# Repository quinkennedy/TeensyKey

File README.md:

One teensy, one key

A small project to attach one keyboard switch to a teensy.
This will be primarily done as a single-sided board for milling
on a hobbyist CNC.

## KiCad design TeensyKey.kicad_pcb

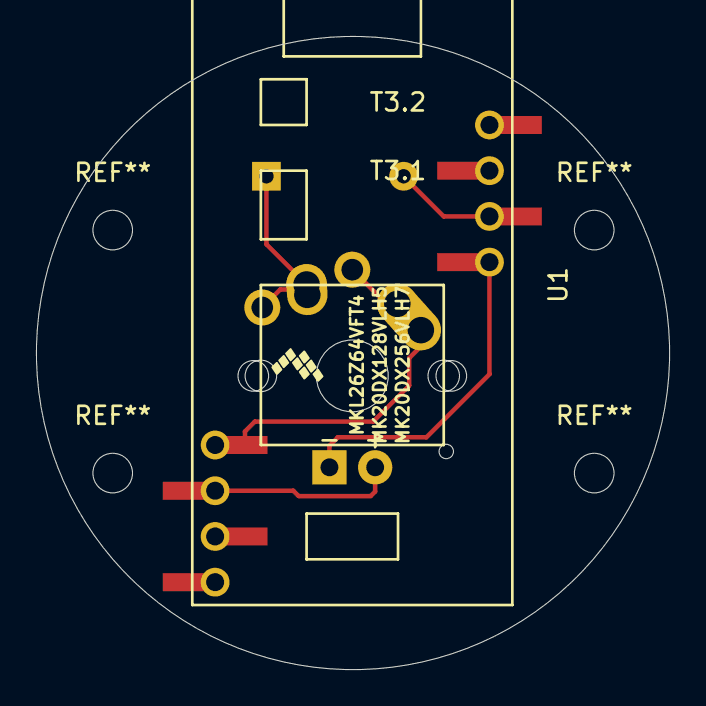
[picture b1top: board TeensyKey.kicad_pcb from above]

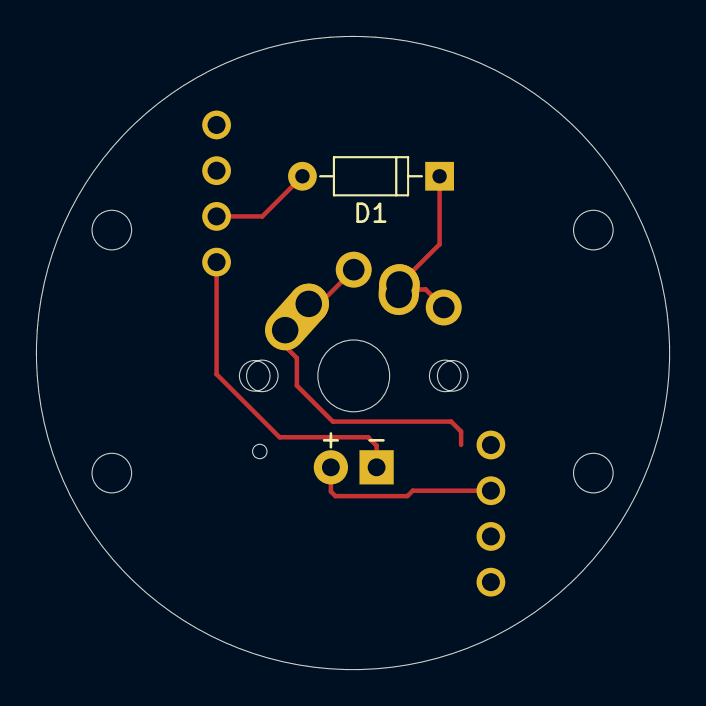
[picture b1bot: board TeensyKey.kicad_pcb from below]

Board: 2 copper layers, 35.2 x 35.2 mm, 3 parts (2 on the bottom side), 5 nets.

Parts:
D1: D; D_DO-35_SOD27_P7.62mm_Horizontal
SW1: MX-with-LED; MX-Alps-Choc-1U
U1: Teensy3.2; Teensy30_31_32_LC_smt_combi

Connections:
unnamed: D1.1, SW1.2
unnamed: D1.2, U1.28
unnamed: SW1.1, U1.11
unnamed: SW1.3, U1.12
unnamed: SW1.4, U1.27

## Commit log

2019-12-09 init
2019-12-10 adding libraries
2019-12-10 documenting submodules
2019-12-10 including teensy symbols
    I'm not sure how to use relative paths for
    including libraries and footprints, so this solution
    isn't perfect.
    also updated the gitignore to a more comprehensive version
2019-12-11 adding switch components & footprints
2019-12-11 adding items to schematic
    switched component & footprint references to be
    project-relative using KIPRJMOD env variable
2019-12-13 adding personalized footprints
2019-12-13 switched footprint to my version
2019-12-13 laid out components
    hid unused SMD pads
2019-12-13 hiding unused THT pins
2019-12-13 added board edge
2019-12-14 routed traces
2019-12-14 added mounting holes
2019-12-14 cleaned up visualization
